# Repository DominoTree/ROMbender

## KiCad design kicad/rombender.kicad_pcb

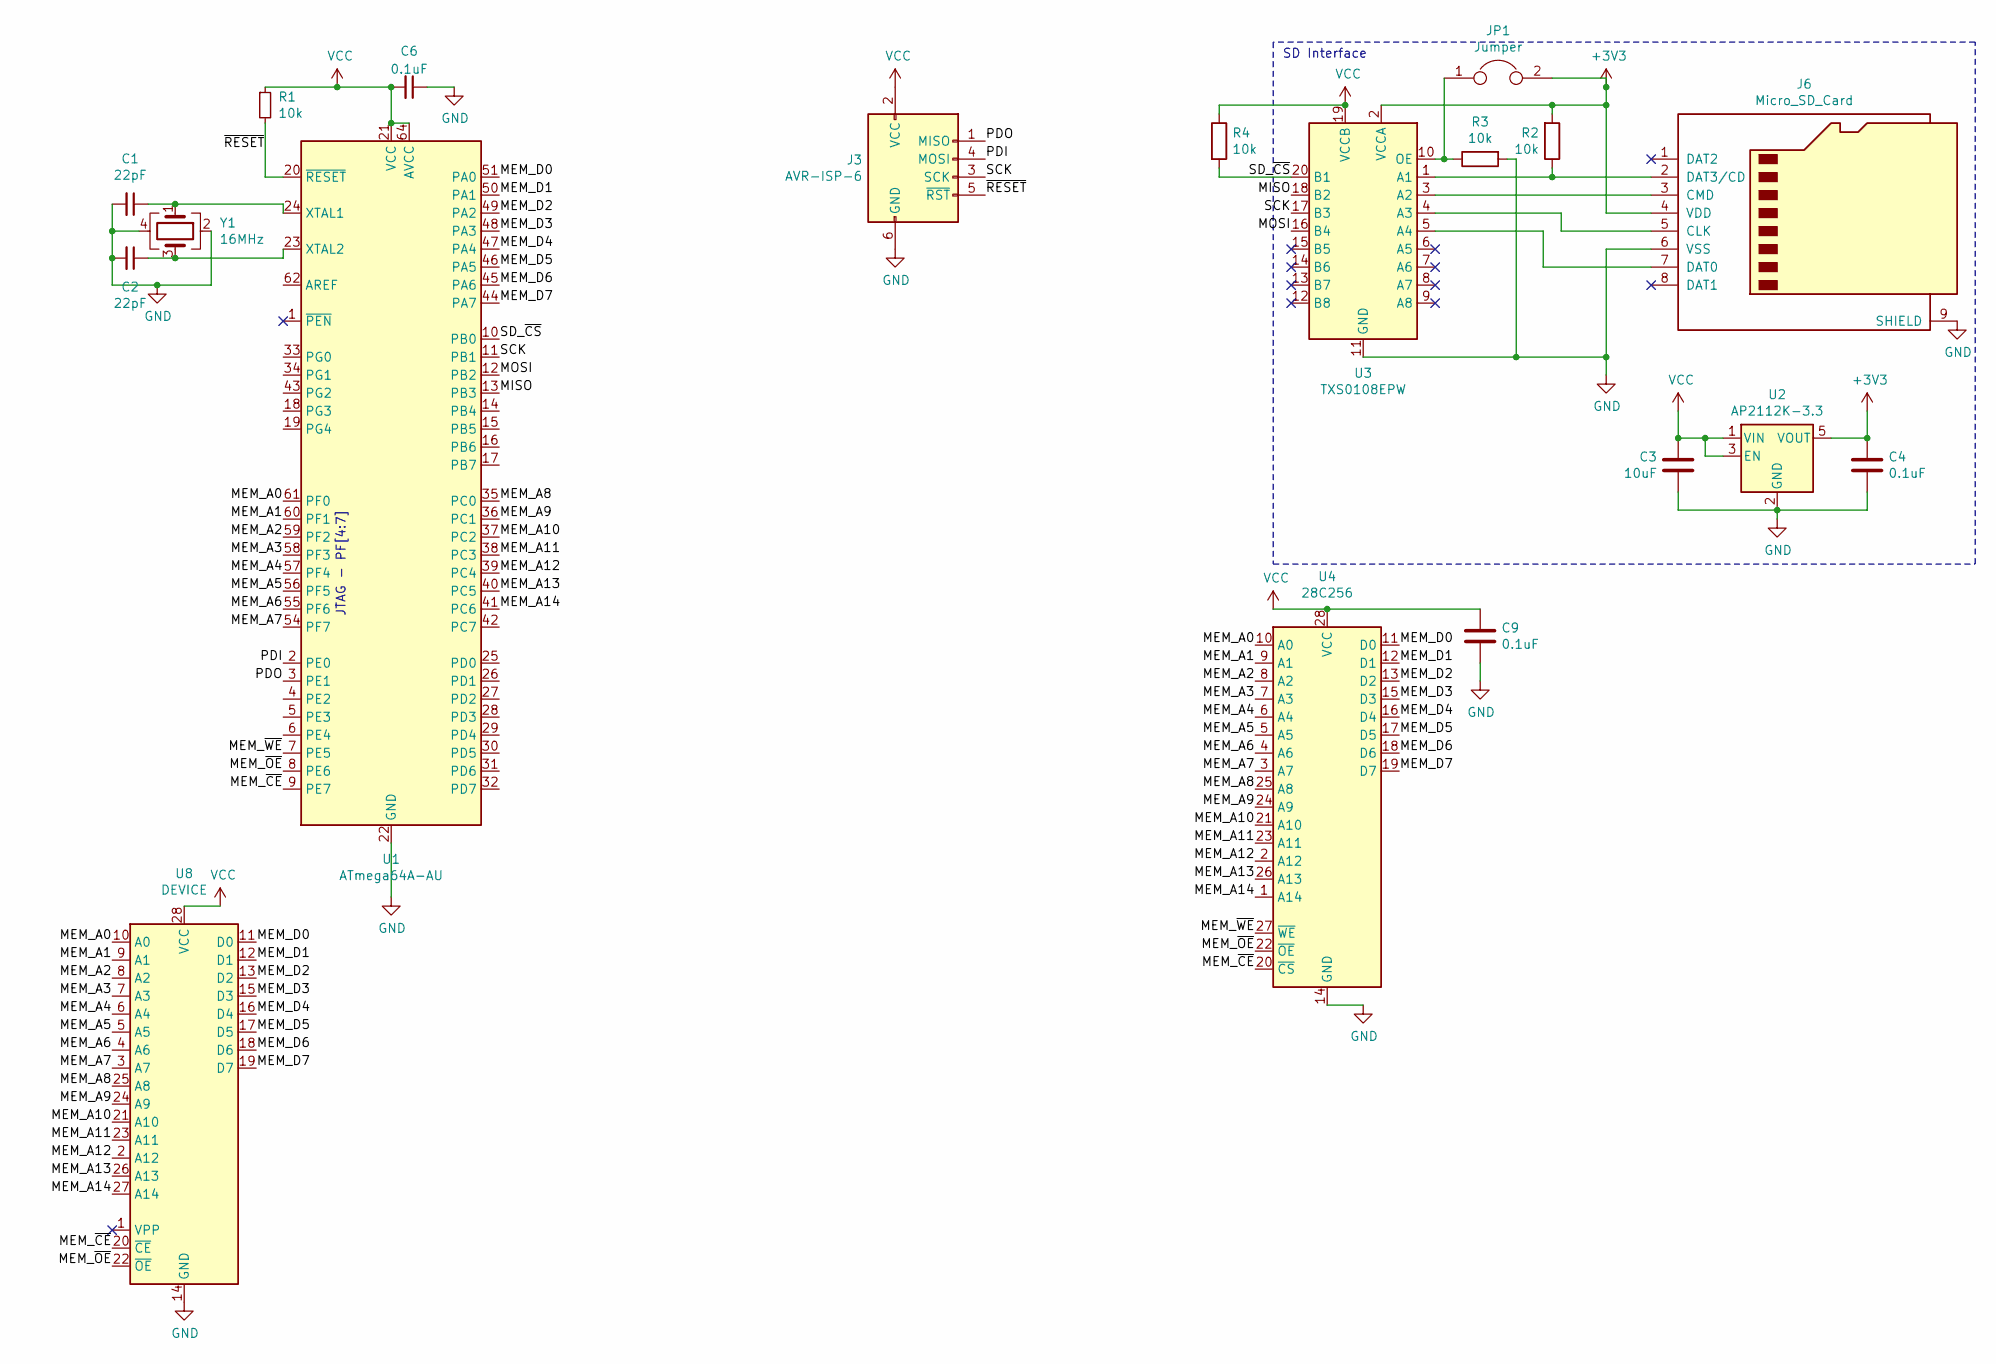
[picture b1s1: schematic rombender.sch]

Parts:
C1, C2: 22pF; C_0603_1608Metric
C3: 10uF; C_0603_1608Metric
C4, C6, C9: 0.1uF; C_0603_1608Metric
J3: AVR-ISP-6; PinHeader_2x03_P2.54mm_Vertical
J6: Micro_SD_Card; microSD_HC_Hirose_DM3D-SF
JP1: Jumper; SolderJumper-2_P1.3mm_Open_TrianglePad1.0x1.5mm
R1, R2, R3, R4: 10k; R_0603_1608Metric
U1: ATmega64A-AU; TQFP-64_14x14mm_P0.8mm
U2: AP2112K-3.3; SOT-23-5
U3: TXS0108EPW; TSSOP-20_4.4x6.5mm_P0.65mm
U4: 28C256; SOIC-28W_7.5x17.9mm_P1.27mm
U8: DEVICE; DIP-28_W15.24mm
Y1: 16MHz; Crystal_SMD_3225-4Pin_3.2x2.5mm

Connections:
+3V3: C4.1, J6.4 (VDD), JP1.2, R2.2, U2.5 (VOUT), U3.2 (VCCA)
/MEM_A0: U1.61 (PF0), U4.10 (A0), U8.10 (A0)
/MEM_A1: U1.60 (PF1), U4.9 (A1), U8.9 (A1)
/MEM_A2: U1.59 (PF2), U4.8 (A2), U8.8 (A2)
/MEM_A3: U1.58 (PF3), U4.7 (A3), U8.7 (A3)
/MEM_A4: U1.57 (PF4), U4.6 (A4), U8.6 (A4)
/MEM_A5: U1.56 (PF5), U4.5 (A5), U8.5 (A5)
/MEM_A6: U1.55 (PF6), U4.4 (A6), U8.4 (A6)
/MEM_A7: U1.54 (PF7), U4.3 (A7), U8.3 (A7)
/MEM_A8: U1.35 (PC0), U4.25 (A8), U8.25 (A8)
/MEM_A9: U1.36 (PC1), U4.24 (A9), U8.24 (A9)
/MEM_A10: U1.37 (PC2), U4.21 (A10), U8.21 (A10)
/MEM_A11: U1.38 (PC3), U4.23 (A11), U8.23 (A11)
/MEM_A12: U1.39 (PC4), U4.2 (A12), U8.2 (A12)
/MEM_A13: U1.40 (PC5), U4.26 (A13), U8.26 (A13)
/MEM_A14: U1.41 (PC6), U4.1 (A14), U8.27 (A14)
/MEM_D0: U1.51 (PA0), U4.11 (D0), U8.11 (D0)
/MEM_D1: U1.50 (PA1), U4.12 (D1), U8.12 (D1)
/MEM_D2: U1.49 (PA2), U4.13 (D2), U8.13 (D2)
/MEM_D3: U1.48 (PA3), U4.15 (D3), U8.15 (D3)
/MEM_D4: U1.47 (PA4), U4.16 (D4), U8.16 (D4)
/MEM_D5: U1.46 (PA5), U4.17 (D5), U8.17 (D5)
/MEM_D6: U1.45 (PA6), U4.18 (D6), U8.18 (D6)
/MEM_D7: U1.44 (PA7), U4.19 (D7), U8.19 (D7)
/MEM_~CE: U1.9 (PE7), U4.20 (~CS), U8.20 (~CE)
/MEM_~OE: U1.8 (PE6), U4.22 (~OE), U8.22 (~OE)
/MEM_~WE: U1.7 (PE5), U4.27 (~WE)
/MISO: U1.13 (PB3), U3.18 (B2)
/MOSI: U1.12 (PB2), U3.16 (B4)
/PDI: J3.4 (MOSI), U1.2 (PE0)
/PDO: J3.1 (MISO), U1.3 (PE1)
/SCK: J3.3 (SCK), U1.11 (PB1), U3.17 (B3)
/SD_~CS: R4.2, U1.10 (PB0), U3.20 (B1)
/~RESET: J3.5 (~RST), R1.2, U1.20 (~RESET)
GND: C1.2, C2.2, C3.2, C4.2, C6.1, C9.1, J3.6 (GND), J6.6 (VSS), J6.9 (SHIELD), R3.2, U1.22 (GND), U1.53 (GND), U1.63 (GND), U2.2 (GND), U3.11 (GND), U4.14 (GND), U8.14 (GND), Y1.2, Y1.4
unnamed: C1.1, U1.24 (XTAL1), Y1.1
unnamed: C2.1, U1.23 (XTAL2), Y1.3
unnamed: J6.2 (DAT3/CD), R2.1, U3.1 (A1)
unnamed: J6.3 (CMD), U3.3 (A2)
unnamed: J6.5 (CLK), U3.4 (A3)
unnamed: J6.7 (DAT0), U3.5 (A4)
unnamed: JP1.1, R3.1, U3.10 (OE)
VCC: C3.1, C6.2, C9.2, J3.2 (VCC), R1.1, R4.1, U1.21 (VCC), U1.52 (VCC), U1.64 (AVCC), U2.1 (VIN), U2.3 (EN), U3.19 (VCCB), U4.28 (VCC), U8.28 (VCC)

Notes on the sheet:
SD Interface
JTAG - PF[4:7]

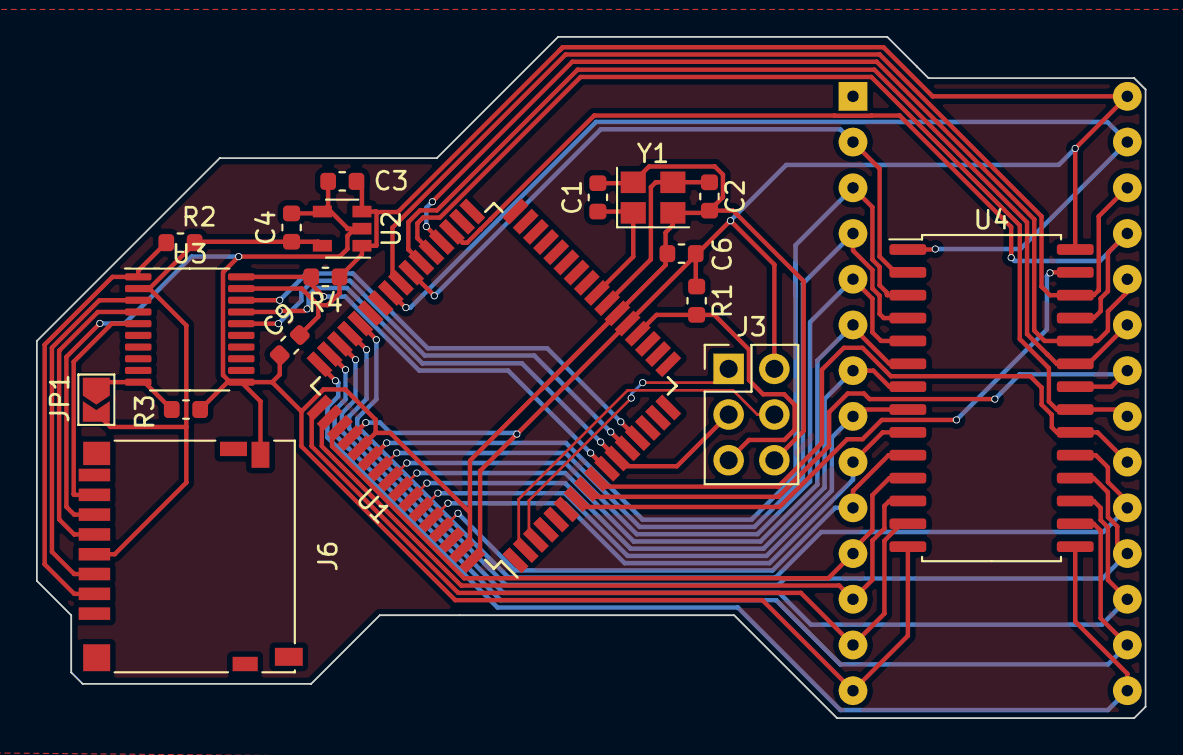
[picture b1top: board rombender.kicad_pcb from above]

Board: 2 copper layers, 61.6 x 37.8 mm, 19 parts (0 on the bottom side), 43 nets.

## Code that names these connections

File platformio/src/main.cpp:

#include <Arduino.h>
#include <SdFat.h>

#include <rom.inc>

#define SD_CS_PIN PB0

SdFat SD;
File sk1ROM;

void set_addr(u16 addr)
{
  PORTF = addr & 255;
  PORTC = addr >> 8;
}

void set_data(byte data)
{
  PORTA = data;
}

void mem_ce(uint8_t state) 
{
  pinMode(PE7, OUTPUT);
  digitalWrite(PE7, state);
}

void mem_oe(uint8_t state) 
{
  pinMode(PE6, OUTPUT);
  digitalWrite(PE6, state);
}

void mem_we(uint8_t state) 
{
  pinMode(PE5, OUTPUT);
  digitalWrite(PE5, state);
}

void write_byte(u16 addr, byte data)
{
  set_addr(addr);
  set_data(data);
  delay(1);
  mem_we(LOW);  //latch addr
  delay(1);
  mem_we(HIGH); //latch data
  delay(1);
}

//AT28C256
void disable_sdp() {
  write_byte(0x5555, 0xAA);
  write_byte(0x2AAA, 0x55);
  write_byte(0x5555, 0x80);
  write_byte(0x5555, 0xAA);
  write_byte(0x2AAA, 0x55);
  write_byte(0x5555, 0x20);
}

//AT28C256
void erase_chip() {
  write_byte(0x5555, 0xAA);
  write_byte(0x2AAA, 0x55);
  write_byte(0x5555, 0x80);
  write_byte(0x5555, 0xAA);
  write_byte(0x2AAA, 0x55);
  write_byte(0x5555, 0x10);
  delay(20);
}

void enable_outputs()
{
  DDRA = 0b11111111; //DATA
  DDRC = 0b01111111; //ADDR_H
  DDRF = 0b11111111; //ADDR_L
}

void disable_outputs()
{
  DDRA = 0b00000000; //DATA
  DDRC = 0b00000000; //ADDR_H
  DDRF = 0b00000000; //ADDR_L
}

void init_rom() {
  //enable the chip
  mem_ce(LOW);
  mem_oe(HIGH);
  for (u16 addr = 0; addr < sk1_rom_bin_len; addr++)
  {
    write_byte(addr, sk1_rom_bin[addr]);
  }
  //lol as a full array it's too big for this avr to address
  write_byte(32767, 0x7c);

  //set CE/OE to tri-state and let the device take over
  //WE doesn't need to go tri-state
  pinMode(PE6, INPUT);
  pinMode(PE7, INPUT);
}

void setup()
{
  mem_we(HIGH);
  Serial.begin(115200);
  enable_outputs();
  delay(20);
  init_rom();
  disable_outputs();

  //turn these on for now
  mem_ce(LOW);
  mem_oe(LOW);
  randomSeed(analogRead(PE1)); //PE1 and PE2 should both be floating
}

void loop()
{
  //just read back one random address every second and see if we get data
  delay(1000);
  u16 rand_addr = random(32767);
  set_addr(rand_addr);
  Serial.print(rand_addr);
  Serial.print(" = ");
  Serial.println(PORTA);
}

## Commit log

2020-10-06 init
2020-10-13 whoops
2020-10-31 'rust'
2020-11-18 simple read test
2020-11-25 bump/fix
